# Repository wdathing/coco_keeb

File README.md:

# CoCo Pico Keyboard Interface

A Raspberry Pi Pico board that connects to the keyboard matrix of a **TRS-80 Color
Computer 3**. Its 16-pin keyboard header (J1) is wired pin-for-pin to the CoCo 3
keyboard connector, so the same board can sit on either side of that connector.
Which firmware you flash decides which way the keystrokes go.

Designed in KiCad. Built and tested.

## Two firmware loads, two directions

| | **1. QMK `coco`** | **2. usb-to-coco** |
|---|---|---|
| Direction | Real CoCo keyboard **→** PC (USB) | Modern USB / Bluetooth keyboard **→** real CoCo |
| J1 connects to | The CoCo 3 **keyboard's** ribbon cable | The CoCo 3 **motherboard's** keyboard connector |
| Pico | Pico (RP2040) | Pico 2 W (RP2350 + Bluetooth) |
| What the Pico does | Scans the matrix and acts as a USB HID keyboard | Acts as a USB / Bluetooth host and emulates the matrix |
| Repository | [wdathing/qmk_firmware → `keyboards/coco`](https://github.com/wdathing/qmk_firmware/tree/master/keyboards/coco) | [wdathing/usb-to-coco](https://github.com/wdathing/usb-to-coco) |
| Build system | QMK (`make coco:default`) | Pico SDK 2.3.0 / CMake |

Both loads use the **same pin assignment** for the matrix (rows on GP0–GP6, columns
on GP8–GP15) and share the same key layout. They are mirror images of each other:
QMK reads the CoCo keyboard and sends modern keycodes, while usb-to-coco takes modern
keycodes and reproduces CoCo key presses.

Both also handle the places where the two keyboards disagree: they remap shifted
symbols so the character on the keycap you're pressing is the one that appears.

---

### 1. QMK `coco`: use a CoCo 3 keyboard on a PC

Plug the original CoCo 3 keyboard into J1 and the Pico's USB port into a PC, a
Raspberry Pi, or a CoCo emulator such as
[XRoar](https://github.com/ugufru/xroar-waveshare-rp2350-pizero). The board shows
up as a standard USB keyboard.

- **CoCo shifted symbols.** On the CoCo, `Shift+2` is `"`, `Shift+7` is `'`,
  `Shift+8` is `(`, `Shift+:` is `*`, `Shift+;` is `+`, and so on. The firmware sends
  whatever is printed on the CoCo keycap, not the PC character in that position.
- **Two layouts, switchable at runtime:**
  - `Ctrl` + `Alt` + `0`: **CoCo layout** (CoCo symbols, the default)
  - `Ctrl` + `Alt` + `1`: **PC layout** (plain PC symbols)

  The selected layout is saved in EEPROM and survives unplugging.
- **Windows / GUI key.** The CoCo has no Windows key, so tapping `Ctrl` + `Alt` together
  and releasing them, with no other key in between, sends one. Holding them still
  works as normal `Ctrl` and `Alt`.
- **Special keys.** `CLEAR` sends `Home` and `BREAK` sends `Esc`. `ALT`, `CTRL`, `F1`,
  and `F2` pass straight through.
- **Joystick.** An Atari-style digital joystick on the DE9 (J2) sends the arrow keys,
  and its fire button sends `Space`:

  | DE9 pin | Function | Pico GPIO | Key sent |
  |---|---|---|---|
  | 1 | Up | GP27 | ↑ |
  | 2 | Down | GP20 | ↓ |
  | 3 | Left | GP21 | ← |
  | 4 | Right | GP22 | → |
  | 6 | Fire | GP26 | Space |
  | 8 | Ground | — | — |

- NKRO, bootmagic, extra keys, and mouse keys are enabled.

**Build and flash**, from a checkout of the QMK fork:

```bash
make coco:default          # builds coco_default.uf2
make coco:default:flash    # or hold BOOTSEL, plug in, and copy the .uf2 over
```

To enter the bootloader without the BOOTSEL button, hold the top-left matrix key
(`@`) while plugging in.

---

### 2. usb-to-coco: use a modern keyboard on a real CoCo 3

Remove the CoCo's own keyboard and plug J1 into the motherboard's keyboard
connector. The Pico 2 W pretends to be the keyboard: it watches which column the
CoCo is scanning and pulls the matching rows low for whatever keys are held. The CoCo
can't tell the difference, so nothing on the CoCo side needs to change.

- **USB keyboards** plug into the Pico's own USB port, which runs in host mode. Use an
  OTG adapter, and power the board through J5.
- **Bluetooth keyboards** work too, both Classic and BLE (tested with an 8BitDo Retro
  Mechanical keyboard and an Anker compact keyboard).
  - Press the **pairing button (SW1)** to open a 60-second pairing window. The Pico
    scans for nearby keyboards and connects to the first one it finds.
  - The last keyboard is remembered and reconnects automatically on power-up.
- **Status LEDs:**
  - **D1** lights while the CoCo is actively scanning the keyboard, so you can confirm
    the CoCo is alive and connected.
  - **D2** lights while any key is held.
- **Keycap-accurate symbols.** On a modern keyboard, `Shift+2` types `@`, `Shift+;`
  types `:`, and the `'`/`"` key types quotes. Each one is translated to the CoCo key
  (with or without CoCo SHIFT) that produces that character.
- **Joystick.** An Atari-style digital joystick on the DE9 (J2) presses arrow keys, or
  `W`/`A`/`S`/`D`, with fire as `Space`. Hold fire and press SW1 to switch modes.
- **Special keys.** `Esc` and `Pause` send BREAK, `Home` sends CLEAR, `Backspace`
  sends ← (the CoCo's erase-left), and `` ` `` sends @.

**Build and flash** with the Pico SDK (or the Raspberry Pi Pico VS Code extension):

```bash
cmake -B build -G Ninja && ninja -C build    # -> build/usb-to-coco.uf2
```

A `-DDEBUG_KEY_LOG=ON` build is available for bring-up without a CoCo. It logs
decoded keys over UART instead of driving the matrix, because GP0/GP1 are both matrix
rows and UART0. See the
[usb-to-coco README](https://github.com/wdathing/usb-to-coco#debug-build) for details.

---

## Key matrix

The scan order matches the CoCo's own PIA keyboard scan: columns are strobed through
`$FF02` (PB0–PB7), and rows are read through `$FF00` (PA0–PA6). J1 matches CN2 on the
CoCo 3 motherboard pin-for-pin, as documented in the Tandy CoCo 3 Service Manual,
Figure 5-9. Pin 3 is unused on both.

- **Rows** (7): GP0 – GP6
- **Columns** (8): GP8 – GP15

```
       col0   col1   col2   col3   col4   col5   col6   col7
row0    @      A      B      C      D      E      F      G
row1    H      I      J      K      L      M      N      O
row2    P      Q      R      S      T      U      V      W
row3    X      Y      Z      Up     Down   Left   Right  Space
row4    0      1      2      3      4      5      6      7
row5    8      9      :      ;      ,      -      .      /
row6   Enter  Clear  Break  Alt    Ctrl   F1     F2     Shift
```

> The CoCo keyboard is a **diode-less** matrix, so pressing certain combinations of
> three or more keys at once can produce ghost keypresses. This comes from the
> original keyboard, not from either firmware.

## Hardware

| Ref | Part | Pico GPIO | Used by |
|---|---|---|---|
| U1 | Raspberry Pi Pico / Pico 2 W | — | both |
| J1 | 1×16 header: CoCo keyboard matrix | GP0–6, GP8–15 | both |
| J3 | 1×16 header, in parallel with J1 | GP0–6, GP8–15 | — |
| J2 | DE9 male, right angle: joystick | GP20–22, GP26–27 | both |
| J6 | 2×5 header: remote DE9 (mirrors J2) | same as J2 | both |
| D1 + R1 | 3 mm LED, 1 kΩ: CoCo scan activity | GP19 | usb-to-coco |
| D2 + R2 | 3 mm LED, 1 kΩ: key held | GP18 | usb-to-coco |
| SW1 | Right-angle tactile switch: Bluetooth pairing | GP7 | usb-to-coco |
| J4 | 1×4 header: optional SSD1306 I²C OLED | GP16 / GP17 | not yet used |
| J5 | 1×2 header: power in (VSYS, GND) | — | usb-to-coco (USB-host mode) |

DE9 pins 1 and 6 go to the Pico's ADC-capable pins (GP27 and GP26), so J2 can also
carry a CoCo analog joystick in the future.

## Repository contents

| Path | What it is |
|---|---|
| `Coco_pico_keyb.kicad_sch` / `.kicad_pcb` / `.kicad_pro` | KiCad schematic, layout, and project |
| `Coco_pico_keyb.step` | 3D model of the assembled board |
| `Coco_pico_keyb.dsn` / `.ses` / `.rules` | Freerouting autorouter exchange files |
| `production/` | JLCPCB fabrication outputs (Gerber zip, BOM, positions, IPC netlist) |
| `Coco_pico_keyb-backups/` | KiCad project backups |

The `production/` files were generated with the
[JLC Plugin for KiCad](https://github.com/bennymeg/JLC-Plugin-for-KiCad). Upload
`production/Coco_pico_keyb.zip` to JLCPCB to order boards.

## Related project

[**xroar-waveshare-rp2350-pizero**](https://github.com/ugufru/xroar-waveshare-rp2350-pizero)
is a CoCo emulator for the Waveshare RP2350-PiZero that takes USB keyboard input.
Paired with the QMK load, it lets an original CoCo 3 keyboard drive the emulator.

## License

Copyright (c) 2025-2026 William Athing.

The hardware design files in this repository are released under the
[CERN Open Hardware Licence v2 – Permissive](LICENSE) (CERN-OHL-P-2.0). You may use,
modify, manufacture, and sell boards based on this design, including commercially, as
long as you keep the copyright and license notices.
This license applies to every version of the design in this repository, including
commits made before the license file was added.

The firmware is licensed separately:

- **usb-to-coco**: MIT License
- **QMK `coco`**: GPL-2.0-or-later, as required by QMK

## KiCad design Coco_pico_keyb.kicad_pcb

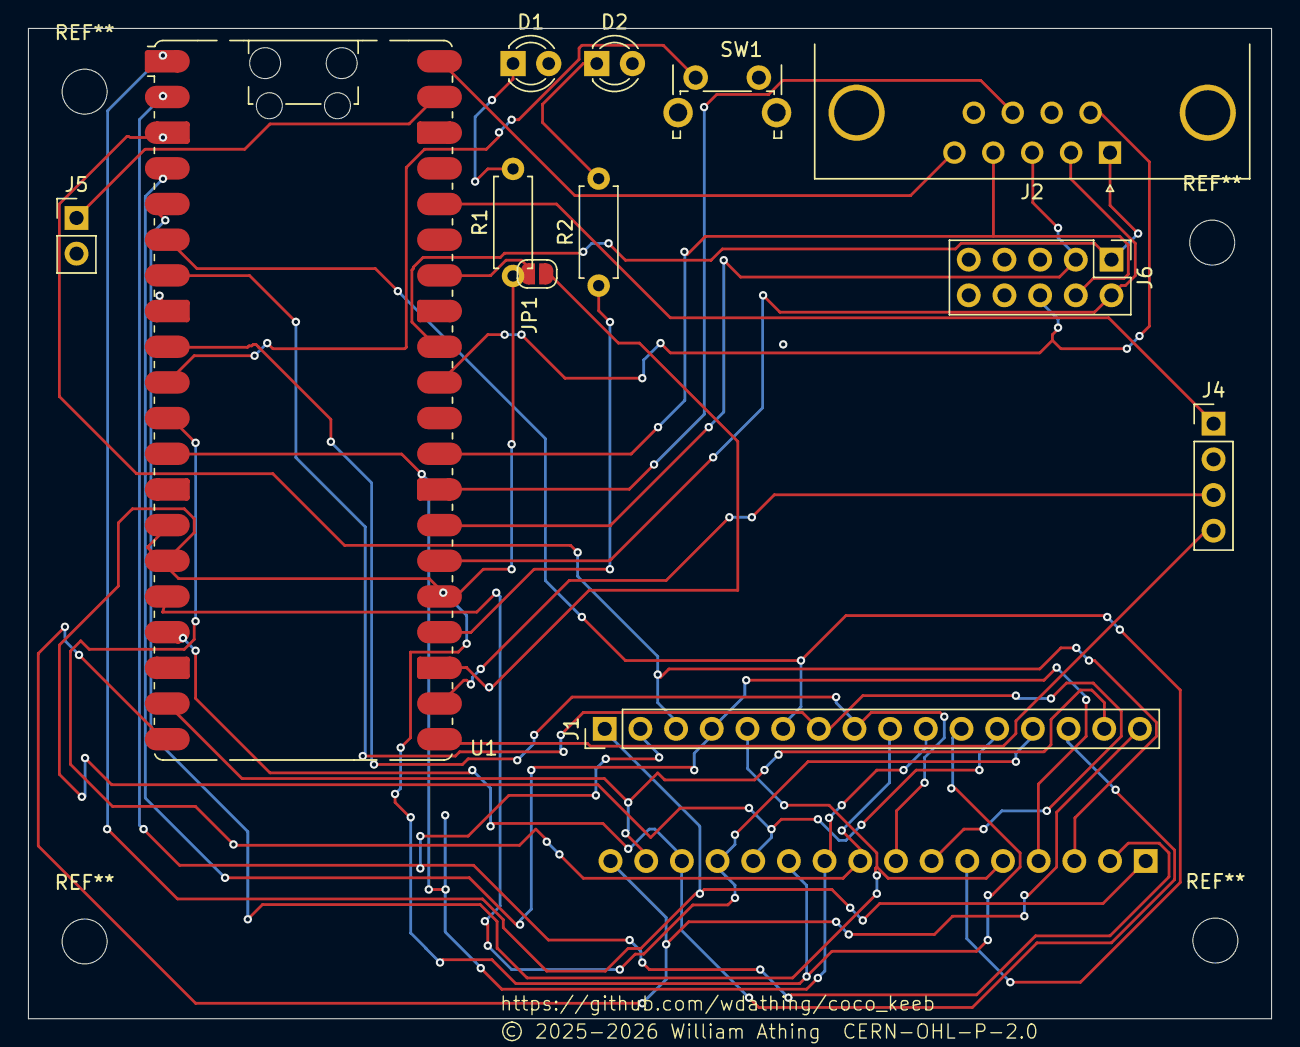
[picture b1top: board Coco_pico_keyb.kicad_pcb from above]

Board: 2 copper layers, 88.5 x 70.5 mm, 13 parts (1 on the bottom side), 34 nets.

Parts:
D1, D2: LED; LED_D3.0mm
J1, J3: Conn_01x16_Pin; PinHeader_1x16_P2.54mm_Vertical
J2: DE9_Plug_MountingHoles; DSUB-9_Pins_Horizontal_P2.77x2.84mm_EdgePinOffset4.94mm_Hou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
J4: SSD1306 I2C Display (optional); PinHeader_1x04_P2.54mm_Vertical
J5: Power In; PinHeader_1x02_P2.54mm_Vertical
J6: Remote DE9; PinHeader_2x05_P2.54mm_Vertical
JP1: OPEN=DRAGON; SolderJumper-2_P1.3mm_Open_RoundedPad1.0x1.5mm
R1, R2: 1K; R_Axial_DIN0207_L6.3mm_D2.5mm_P7.62mm_Horizontal
SW1: Pairing Button; SW_Tactile_SPST_Angled_PTS645Vx39-2LFS
U1: Pico; RaspberryPi_Pico_Common_SMD

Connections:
/3V3: J4.1, U1.36 (3V3)
/BTN_PAIR: SW1.1, U1.10 (GPIO7)
/DRAGON_SEL: JP1.1 (A), U1.34 (GPIO28_ADC2)
/GND: D1.2 (A), D2.2 (A), J4.2, J5.2, J6.8, JP1.2 (B), SW1.2, U1.23 (GND)
/GPIO20: J2.2, J6.2, U1.26 (GPIO20)
/GPIO21: J2.3, J6.3, U1.27 (GPIO21)
/GPIO22: J2.4, J6.4, U1.29 (GPIO22)
/GPIO26_ADC0: J2.6, J6.6, U1.31 (GPIO26_ADC0)
/GPIO27_ADC1: J2.1, J6.1, U1.32 (GPIO27_ADC1)
/I2C0_SCL: J4.3, U1.22 (GPIO17)
/I2C0_SDA: J4.4, U1.21 (GPIO16)
/VSYS: J5.1, U1.39 (VSYS)
unnamed: D1.1 (K), R1.2
unnamed: D2.1 (K), R2.2
unnamed: J1.1, J3.1, U1.1 (GPIO0)
unnamed: J1.2, J3.2, U1.2 (GPIO1)
unnamed: J1.3, J3.3, U1.3 (GND)
unnamed: J1.4, J3.4, U1.4 (GPIO2)
unnamed: J1.5, J3.5, U1.5 (GPIO3)
unnamed: J1.6, J3.6, U1.6 (GPIO4)
unnamed: J1.7, J3.7, U1.7 (GPIO5)
unnamed: J1.8, J3.8, U1.9 (GPIO6)
unnamed: J1.9, J3.9, U1.11 (GPIO8)
unnamed: J1.10, J3.10, U1.12 (GPIO9)
unnamed: J1.11, J3.11, U1.14 (GPIO10)
unnamed: J1.12, J3.12, U1.15 (GPIO11)
unnamed: J1.13, J3.13, U1.16 (GPIO12)
unnamed: J1.14, J3.14, U1.17 (GPIO13)
unnamed: J1.15, J3.15, U1.19 (GPIO14)
unnamed: J1.16, J3.16, U1.20 (GPIO15)
unnamed: J2.8, U1.28 (GND)
unnamed: R2.1, U1.24 (GPIO18)
unnamed: R1.1, U1.25 (GPIO19)
unnamed: J2.5, U1.40 (VBUS)

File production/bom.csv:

Designator,Footprint,Quantity,Value,LCSC Part #
"D1, D2",LED_D3.0mm,2,LED,
"J1, J3",PinHeader_1x16_P2.54mm_Vertical,2,Conn_01x16_Pin,
J2,DSUB-9_Pins_Horizontal_P2.77x2.84mm_EdgePinOffset4.94mm_Housed_MountingHolesOffset4.94mm,1,DE9_Plug_MountingHoles,
J4,PinHeader_1x04_P2.54mm_Vertical,1,SSD1306 I2C Display (optional),
J5,PinHeader_1x02_P2.54mm_Vertical,1,Power In,
J6,PinHeader_2x05_P2.54mm_Vertical,1,Remote DE9,
"R1, R2",R_Axial_DIN0207_L6.3mm_D2.5mm_P7.62mm_Horizontal,2,1K,
SW1,SW_Tactile_SPST_Angled_PTS645Vx39-2LFS,1,Pairing Button,
U1,RaspberryPi_Pico_Common_SMD,1,Pico,

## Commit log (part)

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2025-04-19 first put
2025-05-22 Latest version, first to be built. 100% tested now, works well

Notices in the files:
Coco_pico_keyb.kicad_pcb:
© 2025-2026 William Athing  CERN-OHL-P-2.0
